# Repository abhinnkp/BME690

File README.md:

# BME690 Sensor Module

## Overview

The **BME690 Sensor Module** is an environmental sensing board designed for accurate measurement of atmospheric parameters. It communicates via the **I2C protocol** and supports both **3.3V and 5V operation**, making it suitable for a wide range of embedded and IoT applications.

---

PCB Design File is in KiCAD

---

## Features

* Supports **I2C communication**
* Configurable **I2C address selection**
* Operates on **3.3V and 5V supply**
* Onboard **voltage regulation (5V → 3.3V)**
* Integrated **level shifting for I2C lines**
* Built-in **ESD protection**

---

## Hardware Details

### 1. Power Supply

* The module can be powered using:

  * **3.3V (direct)**
  * **5V input**
* **AP2112K-3.3** LDO regulator is used to convert 5V to 3.3V for the sensor.

---

### 2. I2C Communication

* Communication interface: **I2C**
* Compatible with most microcontrollers (ESP32, STM32, Arduino, etc.)

---

### 3. I2C Address Configuration

The module provides flexible address selection using resistors:

| Resistor Configuration | I2C Address |
| ---------------------- | ----------- |
| R6 = 4.7KΩ             | `0x77`      |
| R7 = 0Ω (0E)           | `0x76`      |

> Note: Populate only one resistor at a time for correct address selection.

---

### 4. Level Shifting

* **BSS138 MOSFETs** are used for bidirectional level shifting
* Ensures safe communication between:

  * 5V logic systems
  * 3.3V sensor

---

### 5. ESD Protection

* **TPD2E2U06DRLR** is used to protect I2C lines from electrostatic discharge (ESD)

---

## Pin Configuration

| Pin Name | Description     |
| -------- | --------------- |
| VCC      | 3.3V / 5V Input |
| GND      | Ground          |
| SDA      | I2C Data Line   |
| SCL      | I2C Clock Line  |

---

## Typical Connection Diagram

```
MCU            BME690 Module
----           --------------
VCC   -------> VCC
GND   -------> GND
SDA   -------> SDA
SCL   -------> SCL
```

---

## Applications

* Environmental monitoring
* Smart home systems
* Industrial IoT
* Weather stations
* Air quality monitoring

---

## Notes

* Ensure correct **I2C address selection** before powering the module
* Do not populate both R6 and R7 simultaneously
* Use proper pull-up resistors if required (typically already present on board)

---

## License

This project is open-source. Feel free to use and modify as per your requirements.

---

## Author

Developed for embedded and IoT applications.

---

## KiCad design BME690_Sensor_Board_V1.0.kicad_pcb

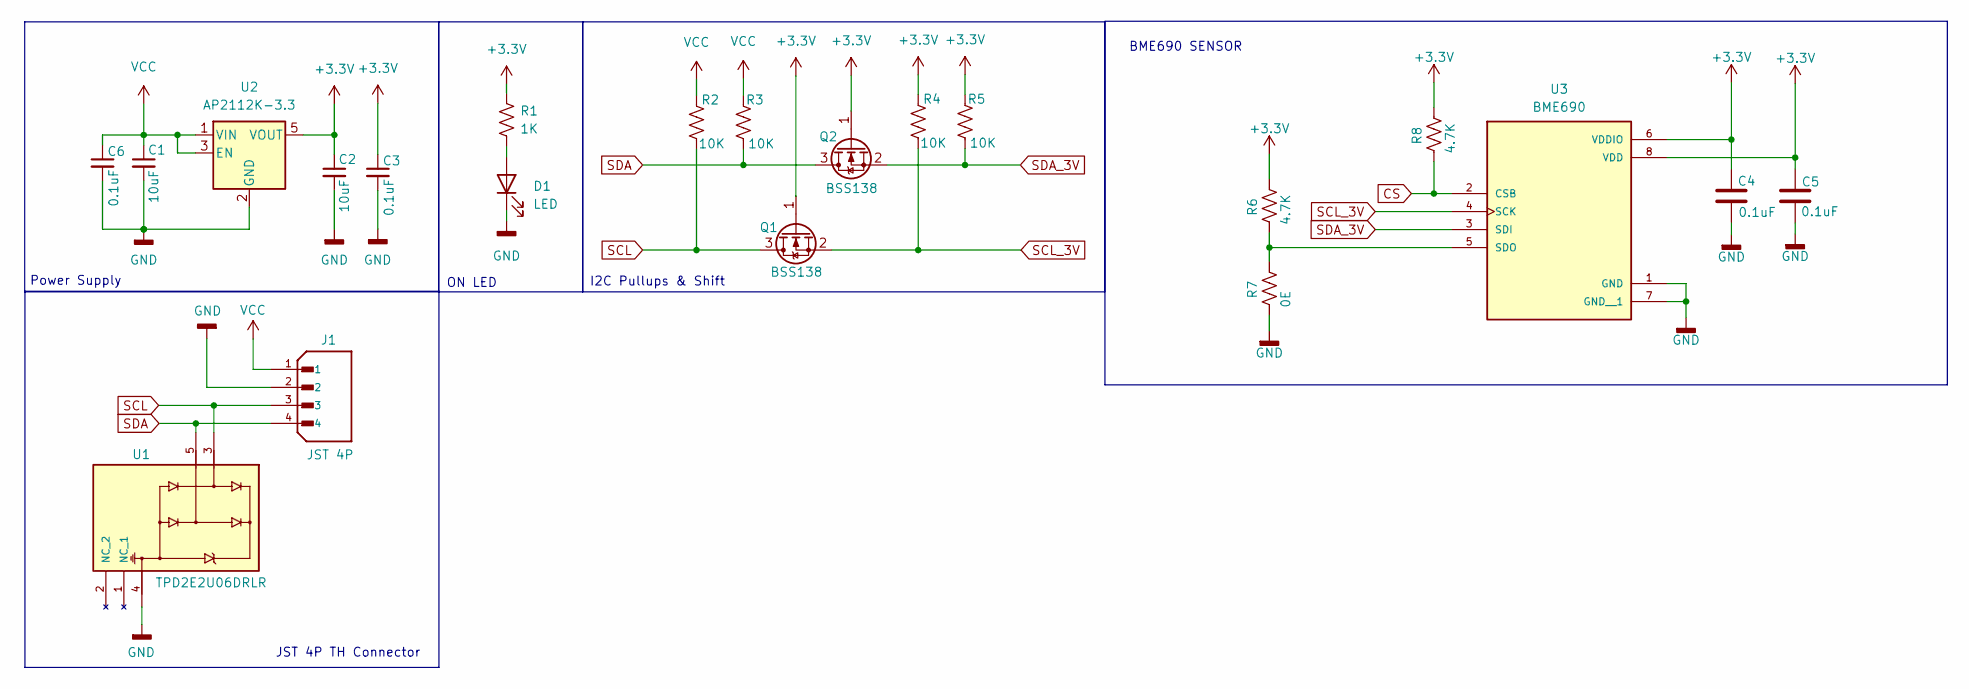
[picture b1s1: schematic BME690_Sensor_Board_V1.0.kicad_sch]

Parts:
C1, C2: 10uF; C_0603_1608Metric_Pad1.08x0.95mm_HandSolder
C3, C4, C5, C6: 0.1uF; C_0603_1608Metric_Pad1.08x0.95mm_HandSolder
D1: LED; LED_0805_2012Metric
J1: JST 4P; JST_S4B-PH-SM4-TB; PARTREV 7/4/21
Q1, Q2: BSS138; SOT-23
R1: 1K; R_0603_1608Metric_Pad0.98x0.95mm_HandSolder
R2, R3, R4, R5: 10K; R_0603_1608Metric_Pad0.98x0.95mm_HandSolder
R6, R8: 4.7K; R_0603_1608Metric_Pad0.98x0.95mm_HandSolder
R7: 0E; R_0603_1608Metric_Pad0.98x0.95mm_HandSolder
U1: TPD2E2U06DRLR; SOTFL50P160X60-5N
U2: AP2112K-3.3; SOT-23-5
U3: BME690; BME690_FP; PARTREV 1.9

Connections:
+3.3V: C2.1, C3.1, C4.1, C5.1, Q1.1 (G), Q2.1 (G), R1.1, R4.1, R5.1, R6.1, R8.1, U2.5 (VOUT), U3.6 (VDDIO), U3.8 (VDD)
CS: R8.2, U3.2 (CSB)
GND: C1.2, C2.2, C3.2, C4.2, C5.2, C6.2, D1.1 (K), J1.2, R7.2, U1.4, U2.2 (GND), U3.1 (GND), U3.7 (GND__1)
unnamed: D1.2 (A), R1.2
unnamed: R6.2, R7.1, U3.5 (SDO)
SCL: J1.3, Q1.3 (D), R2.2, U1.3
SCL_3V: Q1.2 (S), R4.2, U3.4 (SCK)
SDA: J1.4, Q2.3 (D), R3.2, U1.5
SDA_3V: Q2.2 (S), R5.2, U3.3 (SDI)
VCC: C1.1, C6.1, J1.1, R2.1, R3.1, U2.1 (VIN), U2.3 (EN)

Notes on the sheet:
JST 4P TH Connector
Power Supply
ON LED
BME690 SENSOR
I2C Pullups & Shift

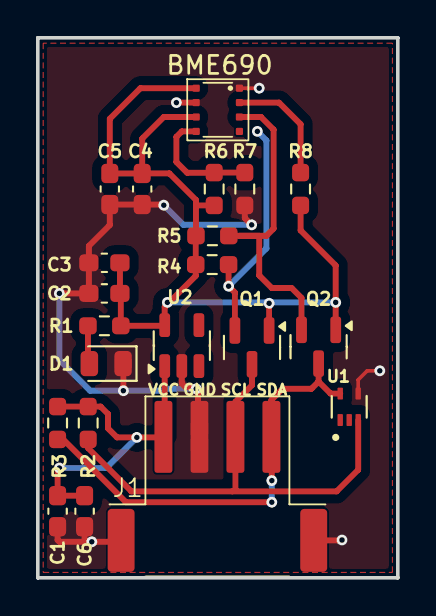
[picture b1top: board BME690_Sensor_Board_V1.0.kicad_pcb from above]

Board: 2 copper layers, 20.0 x 30.0 mm, 21 parts (0 on the bottom side), 10 nets.

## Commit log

2026-03-23 Create Library
